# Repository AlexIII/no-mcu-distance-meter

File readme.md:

# No-MCU Ultrasonic Distance Meter

A Distance Meter that uses no MCU. Bases on ultrasonic ranging module [HC-SR04](https://cdn.sparkfun.com/datasheets/Sensors/Proximity/HCSR04.pdf).

The schematic employs just three standard logic ICs (8-bit counter, divider/oscillator, quad NAND) and a ROM chip (acts as a binary-to-decimal converter).

## Schematic

## Photos

## Video

## Project files

- `no-mcu-distance-meter-kicad5-prj/`  - KiCAD 5.1 project with the schematic and PCB design
- `eprom-programmer`  - Arduino sketch to program the ROM chip using mega2560 (see the sketch for the connections info).

## License

[CC BY-NC 4.0](https://creativecommons.org/licenses/by-nc/4.0/) © github.com/AlexIII

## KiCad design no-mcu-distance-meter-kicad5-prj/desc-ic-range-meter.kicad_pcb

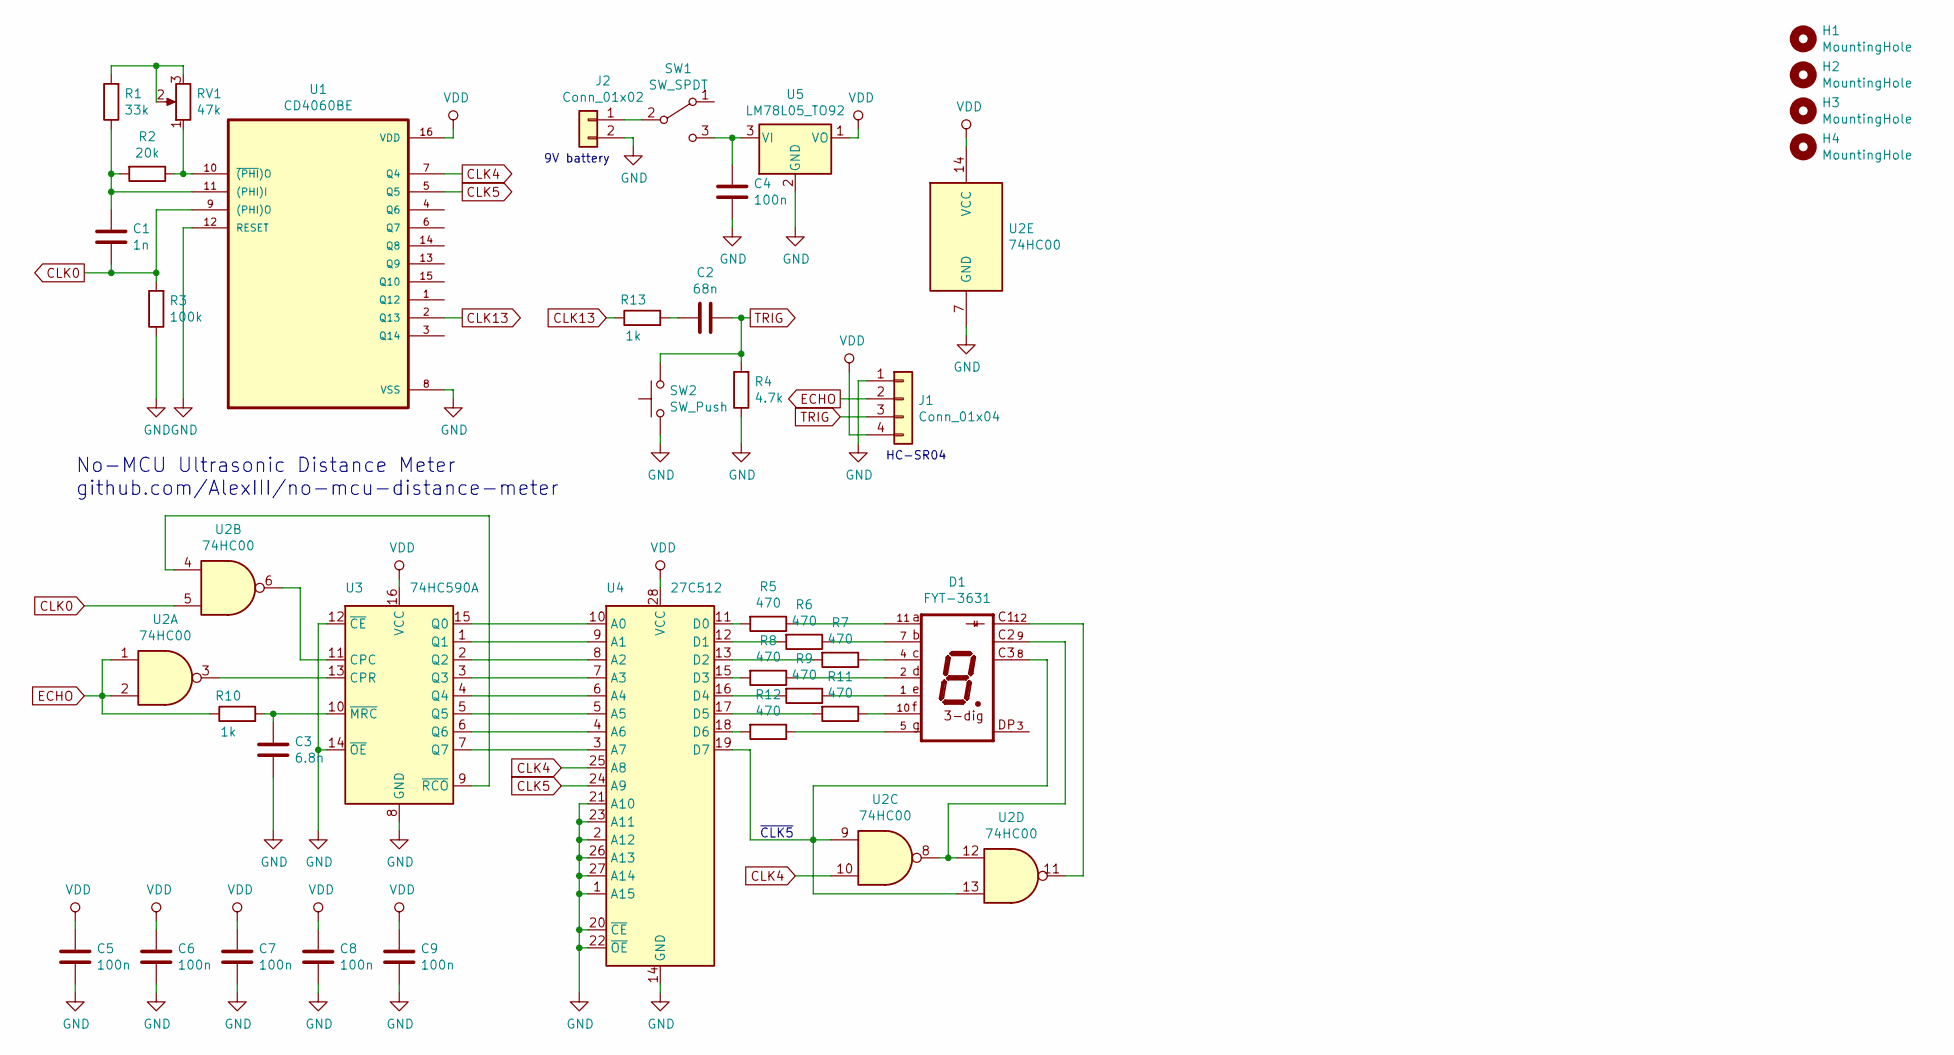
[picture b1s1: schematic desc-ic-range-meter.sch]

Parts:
C1: 1n; C_Disc_D3.0mm_W1.6mm_P2.50mm
C2: 68n; C_Disc_D3.0mm_W1.6mm_P2.50mm
C3: 6.8n; C_Disc_D3.0mm_W1.6mm_P2.50mm
C4, C5, C6, C7, C8, C9: 100n; C_Disc_D3.0mm_W1.6mm_P2.50mm
D1: FYT-3631
H1, H2, H3, H4: MountingHole; MountingHole_3.2mm_M3_Pad
J1: Conn_01x04; Pin_Header_Angled_1x04_Pitch2.54mm
J2: Conn_01x02; Pin_Header_Straight_1x02_Pitch2.54mm
R1: 33k; R_Axial_DIN0207_L6.3mm_D2.5mm_P10.16mm_Horizontal
R2: 20k; R_Axial_DIN0207_L6.3mm_D2.5mm_P10.16mm_Horizontal
R3: 100k; R_Axial_DIN0207_L6.3mm_D2.5mm_P10.16mm_Horizontal
R4: 4.7k; R_Axial_DIN0207_L6.3mm_D2.5mm_P10.16mm_Horizontal
R5, R6, R7, R8, R9, R11, R12: 470; R_Axial_DIN0207_L6.3mm_D2.5mm_P10.16mm_Horizontal
R10, R13: 1k; R_Axial_DIN0207_L6.3mm_D2.5mm_P10.16mm_Horizontal
RV1: 47k; Potentiometer_Trimmer_ACP_CA6v_Horizontal
SW1: SW_SPDT; SK-12F14
SW2: SW_Push; SW_PUSH_6mm
U1: CD4060BE; DIP-16_W7.62mm
U2: 74HC00; DIP-14_W7.62mm
U3: 74HC590A; DIP-16_W7.62mm
U4: 27C512; DIP-28_W15.24mm
U5: LM78L05_TO92; TO-92_Inline_Wide

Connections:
CLK0: C1.2, R3.2, U1.9 ((PHI)O), U2.5
CLK4: U1.7 (Q4), U2.10, U4.25 (A8)
CLK5: U1.5 (Q5), U4.24 (A9)
CLK13: R13.1, U1.2 (Q13)
ECHO: J1.2, R10.1, U2.1, U2.2
GND: C3.1, C4.1, C5.1, C6.1, C7.1, C8.1, C9.1, J1.1, J2.2, R3.1, R4.1, SW2.1, U1.8 (VSS), U1.12 (RESET), U2.7 (GND), U3.8 (GND), U3.12 (~CE), U3.14 (~OE), U4.1 (A15), U4.2 (A12), U4.14 (GND), U4.20 (~CE), U4.21 (A10), U4.22 (~OE), U4.23 (A11), U4.26 (A13), U4.27 (A14), U5.2 (GND)
unnamed: C1.1, R1.1, R2.2, U1.11 ((PHI)I)
unnamed: C2.2, R13.2
unnamed: C3.2, R10.2, U3.10 (~MRC)
unnamed: C4.2, SW1.3 (C), U5.3 (VI)
unnamed: D1.1, R9.1
unnamed: D1.2, R8.1
unnamed: D1.4, R7.1
unnamed: D1.5, R12.1
unnamed: D1.7, R6.1
unnamed: D1.8, U2.9, U2.13, U4.19 (D7)
unnamed: D1.9, U2.8, U2.12
unnamed: D1.10, R11.1
unnamed: D1.11, R5.1
unnamed: D1.12, U2.11
unnamed: J2.1, SW1.2 (B)
unnamed: R1.2, RV1.2, RV1.3
unnamed: R2.1, RV1.1, U1.10 (~(PHI)O)
unnamed: R5.2, U4.11 (D0)
unnamed: R6.2, U4.12 (D1)
unnamed: R7.2, U4.13 (D2)
unnamed: R8.2, U4.15 (D3)
unnamed: R9.2, U4.16 (D4)
unnamed: R11.2, U4.17 (D5)
unnamed: R12.2, U4.18 (D6)
unnamed: U2.3, U3.13 (CPR)
unnamed: U2.4, U3.9 (~RCO)
unnamed: U2.6, U3.11 (CPC)
unnamed: U3.1 (Q1), U4.9 (A1)
unnamed: U3.2 (Q2), U4.8 (A2)
unnamed: U3.3 (Q3), U4.7 (A3)
unnamed: U3.4 (Q4), U4.6 (A4)
unnamed: U3.5 (Q5), U4.5 (A5)
unnamed: U3.6 (Q6), U4.4 (A6)
unnamed: U3.7 (Q7), U4.3 (A7)
unnamed: U3.15 (Q0), U4.10 (A0)
TRIG: C2.1, J1.3, R4.2, SW2.2
VDD: C5.2, C6.2, C7.2, C8.2, C9.2, J1.4, U1.16 (VDD), U2.14 (VCC), U3.16 (VCC), U4.28 (VCC), U5.1 (VO)

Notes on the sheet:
~CLK5
No-MCU Ultrasonic Distance Meter github.com/AlexIII/no-mcu-distance-meter
HC-SR04
9V battery

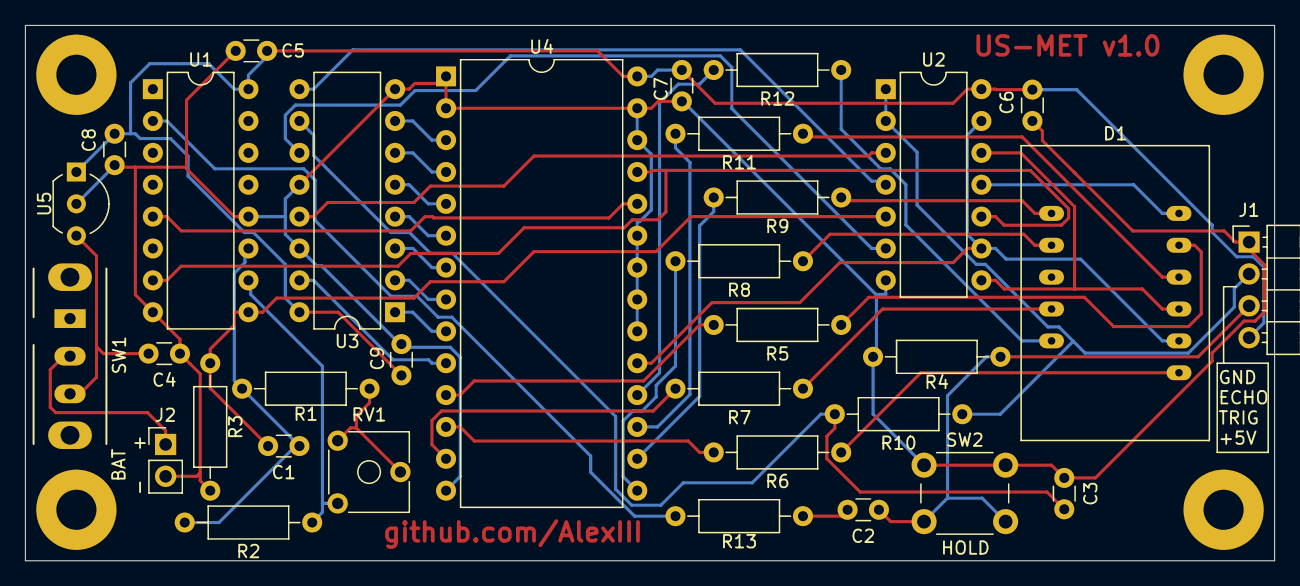
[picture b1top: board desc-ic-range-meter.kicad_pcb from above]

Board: 2 copper layers, 99.6 x 42.7 mm, 37 parts (0 on the bottom side), 43 nets.
